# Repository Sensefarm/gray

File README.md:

# Gray
Development of Gray hardware and software

Gray is an outdoor box that contains and connects to agriculture and smart city sensors.
As my ambitions are a bit larger than my time and to promote innovation in this area, I'm publishing it on the internet as a trial with a MIT license.

## Version control
We use a version of git-flow to keep things nice, tidy and traceable to issues. https://docs.github.com/en/get-started/quickstart/github-flow 
1. Create a separate issue for everything you intend to do. ( assume it's issue 1, and it's about new files)
2. Create a branch from that issue ( call the branch 1-new-files. If using github website this will happen automatically.)
3. Checkout the branch locally, add the files, do a "git add *files*", do a "git commit -m '#1 added new files'", "git push"
4. Find the branch on github, and create a merge request. 
5. Merge the branch, delete the branch (so the github website does not end up listing too many old branches), close the issue (github will do most things for you).

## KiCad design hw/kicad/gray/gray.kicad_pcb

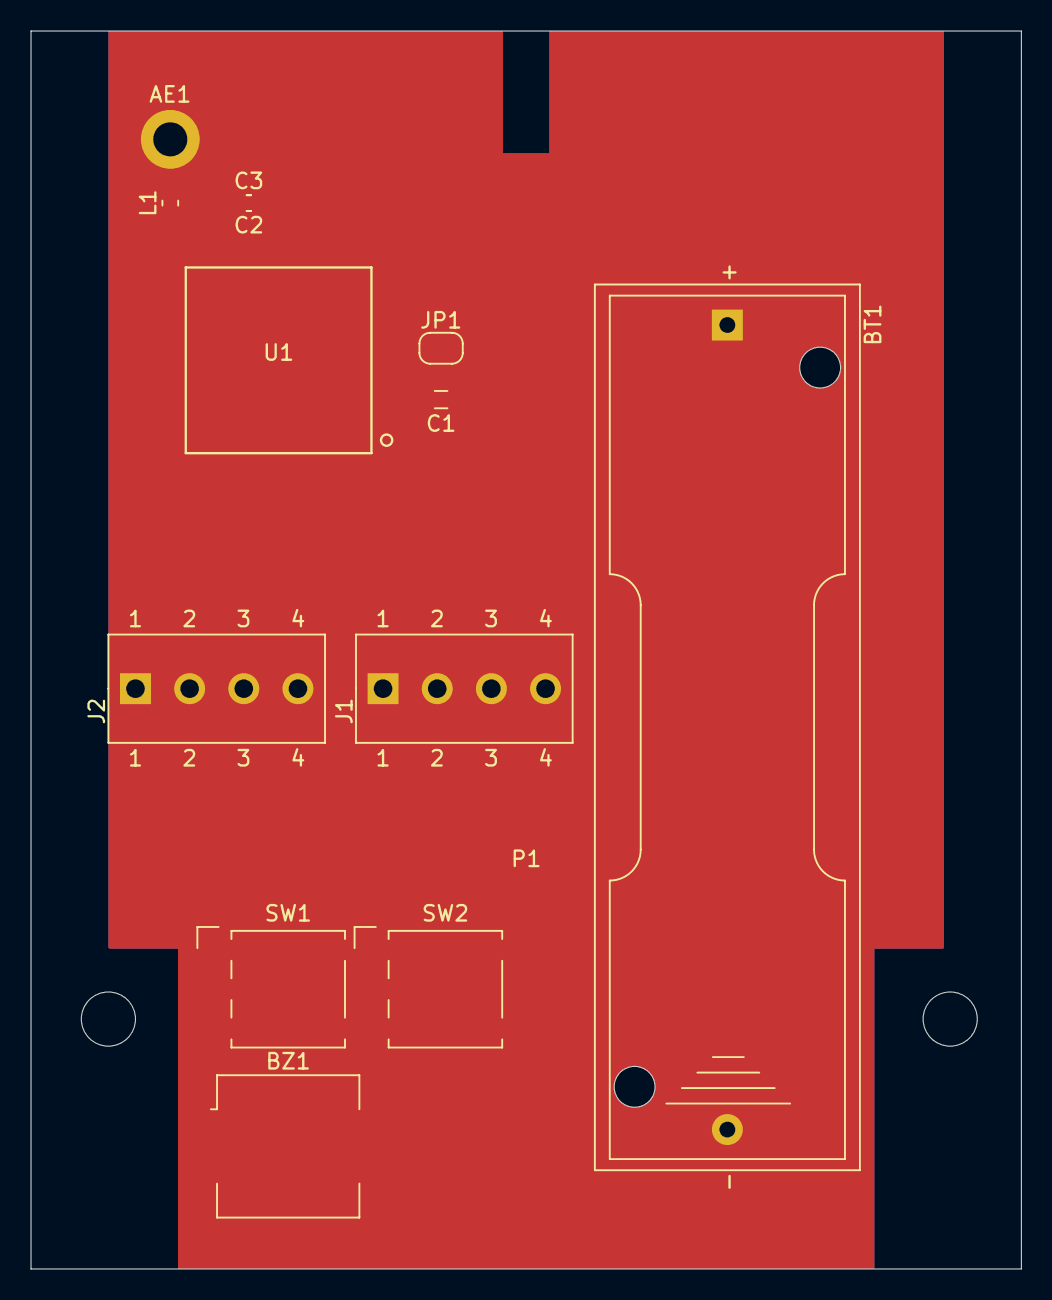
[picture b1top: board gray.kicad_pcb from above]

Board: 2 copper layers, 64.0 x 80.0 mm, 14 parts (0 on the bottom side), 6 nets, no tracks yet.

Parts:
AE1: Antenna; MountingHole_2.2mm_M2_DIN965_Pad
BT1: Battery_Cell; BatteryHolder_Keystone_2460_1xAA
BZ1: Buzzer; Buzzer_CUI_CPT-9019S-SMT
C1: 4u7; L_0805_2012Metric_Pad1.05x1.20mm_HandSolder
C2, C3: C; C_0603_1608Metric_Pad1.08x0.95mm_HandSolder
J1, J2: connector-4p-3mm5
JP1: SolderJumper_2_Bridged; SolderJumper-2_P1.3mm_Bridged_RoundedPad1.0x1.5mm
L1: L; L_0603_1608Metric
P1: gray_pcb
SW1, SW2: SW_Coded_SH-7080; Nidec_Copal_SH-7040B
U1: LoRa-E5

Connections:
+3.3V: C1.1, JP1.2 (B), U1.1 (VCC)
+BATT: BT1.1 (+), JP1.1 (A)
GND: BT1.2 (-), BZ1.2 (+), C1.2, C2.2, C3.2, U1.2 (GND), U1.14 (GND), U1.16 (GND), U1.22 (GND)
unnamed: AE1.1 (A), C3.1, L1.2
unnamed: C2.1, L1.1, U1.15 (RFIO)
unnamed: BZ1.1 (-), U1.20 (PB10)

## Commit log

2022-07-10 #1 first files and structure
2022-07-10 Update README.md
    #1 Updated readme files with branching model for git.
2022-07-10 Changed name to capital letter
2023-11-20 #10 added screw connector datasheet
2024-01-31 issue #10 temporary board to be able to work from home
2024-12-27 Created by OWASP Threat Dragon
2024-12-27 Updated by OWASP Threat Dragon
